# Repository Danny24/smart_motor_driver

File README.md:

# Smart Motor Driver
This motor driver is designed to be interfaced from a host microcontroller by I2C and be able to control the motor with a PID autonomously.

This is a smart motor driver designed to run a Pololu micro gearmotor, the objective of this board is to be able to implement a PID control over this motors with the corresponding RPM feedback using a hall effect sensor. So it must have his own microcontroller and H bridge to be capable of do the work by itself.

The host microcontroller (or any system that can use I2C) will communicate by I2C in order to give the commands to the smart driver module, this includes speed and direction of the motor. The module will automatically implement the PID to maintain the speed and apply more/less power in the motor to achieve that.

Also the control module will be capable of driving the motor for a desired distance and then stop when is reached. To do that you must specify the diameter of your wheel and the gearbox ratio.

This is a project under development, so please follow me to get updates :) This is an open source project, so if you have any ideas to improve it you are welcome!

Check out the project details on Hackaday: https://hackaday.io/project/158429-smart-motor-driver-for-robotics

Thank you for support :)

<br />This work is licensed under a <a rel="license" href="http://creativecommons.org/licenses/by-sa/2.0/">Creative Commons Attribution-ShareAlike 2.0 Generic License</a>.

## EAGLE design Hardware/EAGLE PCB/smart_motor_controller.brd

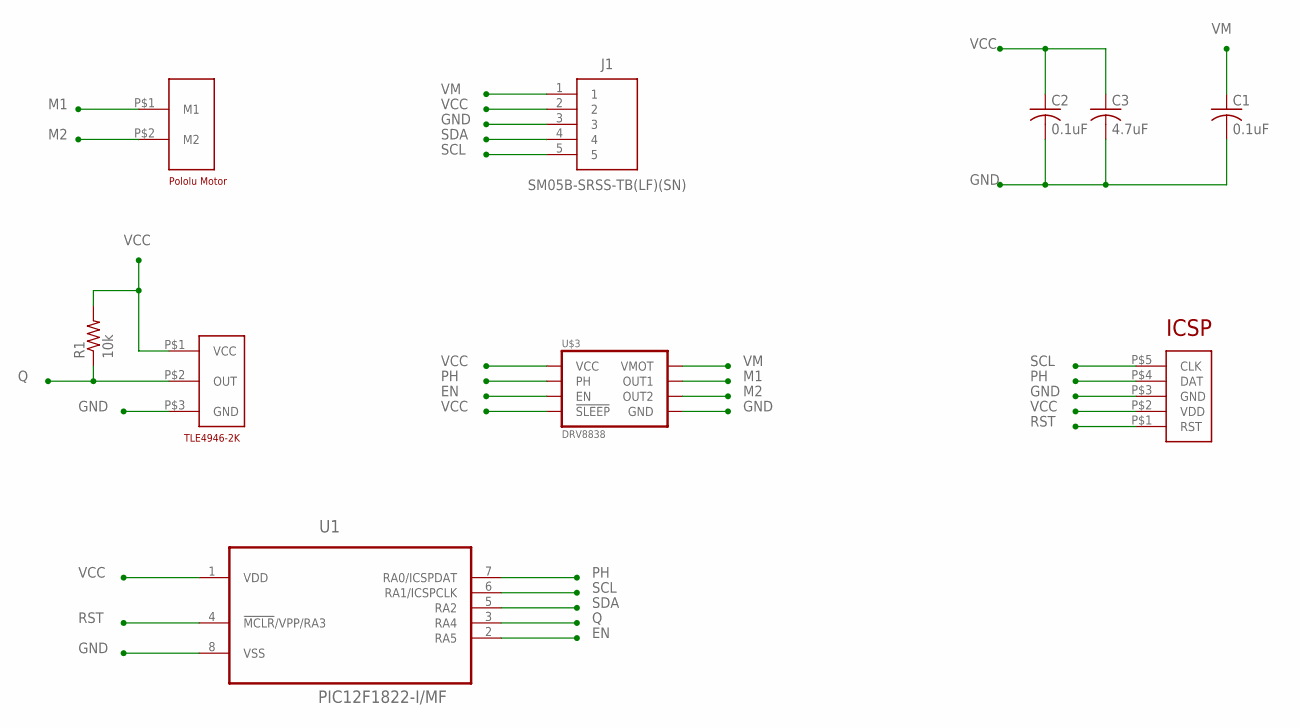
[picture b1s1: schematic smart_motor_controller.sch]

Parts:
C1, C2: 0.1uF; C0603K
C3: 4.7uF; C0805K
J1: SM05B-SRSS-TB(LF)(SN)
R1: 10k; R0805
U1: PIC12F1822-I/MF; DFN300X300X100-9N
U$1: ICSP_POGO
U$3: DRV8838; DSG
U$4: TLE4946-2K; SC59
U$5: POLOLU-MOTOR-BACK; POLOL-MOTOR-BACK

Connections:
EN: U1.2 (RA5), U$3.5 (EN)
GND: C1.2, C2.2, C3.2, J1.3, U1.8 (VSS), U$1.P$3 (GND), U$3.4 (GND), U$3.PAD (GND), U$4.P$3 (GND)
M1: U$3.2 (OUT1), U$5.P$1 (M1)
M2: U$3.3 (OUT2), U$5.P$2 (M2)
PH: U1.7 (RA0/ICSPDAT), U$1.P$4 (DAT), U$3.6 (PH)
Q: R1.1, U1.3 (RA4), U$4.P$2 (OUT)
RST: U1.4 (!MCLR!/VPP/RA3), U$1.P$1 (RST)
SCL: J1.5, U1.6 (RA1/ICSPCLK), U$1.P$5 (CLK)
SDA: J1.4, U1.5 (RA2)
VCC: C2.1, C3.1, J1.2, R1.2, U1.1 (VDD), U$1.P$2 (VDD), U$3.7 (!SLEEP), U$3.8 (VCC), U$4.P$1 (VCC)
VM: C1.1, J1.1, U$3.1 (VMOT)

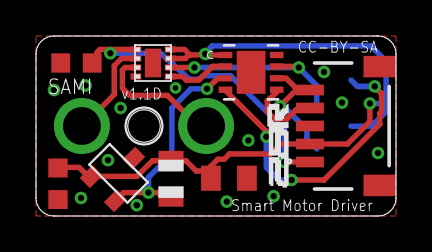
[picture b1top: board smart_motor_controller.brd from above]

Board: 2 copper layers, 20.0 x 10.0 mm, 10 parts (1 on the bottom side), 11 nets.

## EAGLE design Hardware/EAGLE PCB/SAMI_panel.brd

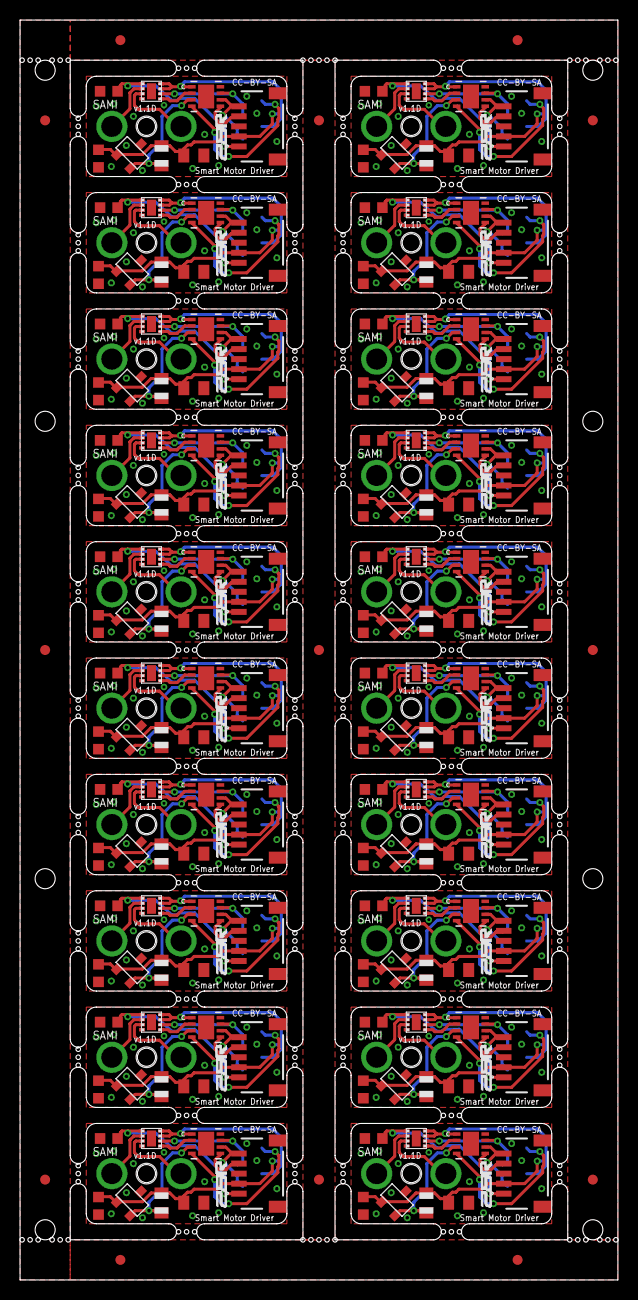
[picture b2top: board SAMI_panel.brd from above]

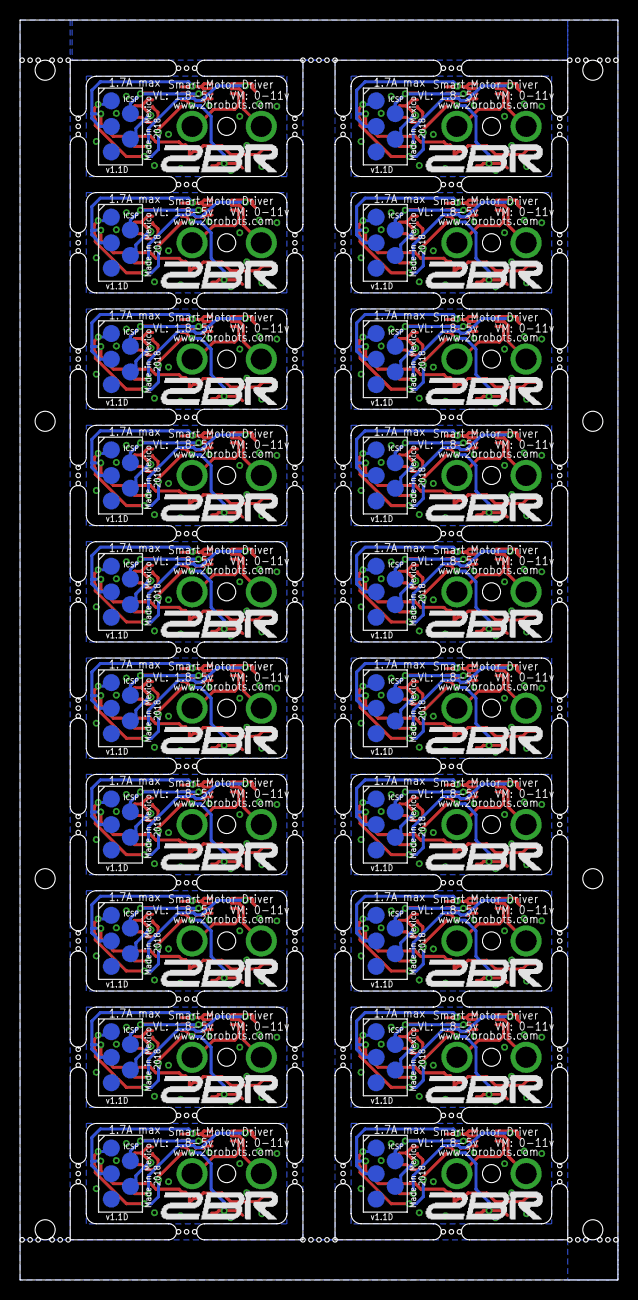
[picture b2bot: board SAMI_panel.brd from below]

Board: 2 copper layers, 59.6 x 125.6 mm, 213 parts (20 on the bottom side), 220 nets.

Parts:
C1, C2, C4, C5, C7, C8, C10, C11, C13, C14, C16, C17, C19, C20, C22, C23, C25, C26, C28, C29, C31, C32, C34, C35, C37, C38, C40, C41, C43, C44, C46, C47, C49, C50, C52, C53, C55, C56, C58, C59: 0.1uF; C0603K
C3, C6, C9, C12, C15, C18, C21, C24, C27, C30, C33, C36, C39, C42, C45, C48, C51, C54, C57, C60: 4.7uF; C0805K
E$1, E$2, E$3, E$4, E$5, E$6, E$7, E$8, E$9, E$10, E$11, E$12, E$13: FIDUCIAL
J1, J2, J3, J4, J5, J6, J7, J8, J9, J10, J11, J12, J13, J14, J15, J16, J17, J18, J19, J20: SM05B-SRSS-TB(LF)(SN)
R1, R2, R3, R4, R5, R6, R7, R8, R9, R10, R11, R12, R13, R14, R15, R16, R17, R18, R19, R20: 10k; R0805
U1, U2, U3, U4, U5, U6, U7, U8, U9, U10, U11, U12, U13, U14, U15, U16, U17, U18, U19, U20: PIC12F1822-I/MF; DFN300X300X100-9N
U$1, U$2, U$9, U$13, U$17, U$21, U$25, U$29, U$33, U$37, U$41, U$45, U$49, U$53, U$57, U$61, U$65, U$69, U$73, U$77: ICSP_POGO
U$3, U$6, U$10, U$14, U$18, U$22, U$26, U$30, U$34, U$38, U$42, U$46, U$50, U$54, U$58, U$62, U$66, U$70, U$74, U$78: DRV8838; DSG
U$4, U$7, U$11, U$15, U$19, U$23, U$27, U$31, U$35, U$39, U$43, U$47, U$51, U$55, U$59, U$63, U$67, U$71, U$75, U$79: TLE4946-2K; SC59
U$5, U$8, U$12, U$16, U$20, U$24, U$28, U$32, U$36, U$40, U$44, U$48, U$52, U$56, U$60, U$64, U$68, U$72, U$76, U$80: POLOLU-MOTOR-BACK; POLOL-MOTOR-BACK

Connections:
EN: U1.2, U$3.5
EN1: U2.2, U$6.5
EN2: U3.2, U$10.5
EN3: U4.2, U$14.5
EN4: U5.2, U$18.5
EN5: U6.2, U$22.5
EN6: U7.2, U$26.5
EN7: U8.2, U$30.5
EN8: U9.2, U$34.5
EN9: U10.2, U$38.5
EN10: U11.2, U$42.5
EN11: U12.2, U$46.5
EN12: U13.2, U$50.5
EN13: U14.2, U$54.5
EN14: U15.2, U$58.5
EN15: U16.2, U$62.5
EN16: U17.2, U$66.5
EN17: U18.2, U$70.5
EN18: U19.2, U$74.5
EN19: U20.2, U$78.5
GND: C1.2, C2.2, C3.2, J1.3, U1.8, U$1.P$3, U$3.4, U$3.PAD, U$4.P$3
GND1: C4.2, C5.2, C6.2, J2.3, U2.8, U$2.P$3, U$6.4, U$6.PAD, U$7.P$3
GND2: C7.2, C8.2, C9.2, J3.3, U3.8, U$9.P$3, U$10.4, U$10.PAD, U$11.P$3
GND3: C10.2, C11.2, C12.2, J4.3, U4.8, U$13.P$3, U$14.4, U$14.PAD, U$15.P$3
GND4: C13.2, C14.2, C15.2, J5.3, U5.8, U$17.P$3, U$18.4, U$18.PAD, U$19.P$3
GND5: C16.2, C17.2, C18.2, J6.3, U6.8, U$21.P$3, U$22.4, U$22.PAD, U$23.P$3
GND6: C19.2, C20.2, C21.2, J7.3, U7.8, U$25.P$3, U$26.4, U$26.PAD, U$27.P$3
GND7: C22.2, C23.2, C24.2, J8.3, U8.8, U$29.P$3, U$30.4, U$30.PAD, U$31.P$3
GND8: C25.2, C26.2, C27.2, J9.3, U9.8, U$33.P$3, U$34.4, U$34.PAD, U$35.P$3
GND9: C28.2, C29.2, C30.2, J10.3, U10.8, U$37.P$3, U$38.4, U$38.PAD, U$39.P$3
GND10: C31.2, C32.2, C33.2, J11.3, U11.8, U$41.P$3, U$42.4, U$42.PAD, U$43.P$3
GND11: C34.2, C35.2, C36.2, J12.3, U12.8, U$45.P$3, U$46.4, U$46.PAD, U$47.P$3
GND12: C37.2, C38.2, C39.2, J13.3, U13.8, U$49.P$3, U$50.4, U$50.PAD, U$51.P$3
GND13: C40.2, C41.2, C42.2, J14.3, U14.8, U$53.P$3, U$54.4, U$54.PAD, U$55.P$3
GND14: C43.2, C44.2, C45.2, J15.3, U15.8, U$57.P$3, U$58.4, U$58.PAD, U$59.P$3
GND15: C46.2, C47.2, C48.2, J16.3, U16.8, U$61.P$3, U$62.4, U$62.PAD, U$63.P$3
GND16: C49.2, C50.2, C51.2, J17.3, U17.8, U$65.P$3, U$66.4, U$66.PAD, U$67.P$3
GND17: C52.2, C53.2, C54.2, J18.3, U18.8, U$69.P$3, U$70.4, U$70.PAD, U$71.P$3
GND18: C55.2, C56.2, C57.2, J19.3, U19.8, U$73.P$3, U$74.4, U$74.PAD, U$75.P$3
GND19: C58.2, C59.2, C60.2, J20.3, U20.8, U$77.P$3, U$78.4, U$78.PAD, U$79.P$3
M1: U$3.2, U$5.P$1
M2: U$3.3, U$5.P$2
M3: U$6.3, U$8.P$2
M4: U$6.2, U$8.P$1
M5: U$10.3, U$12.P$2
M6: U$10.2, U$12.P$1
M7: U$14.3, U$16.P$2
M8: U$14.2, U$16.P$1
M9: U$18.3, U$20.P$2
M10: U$18.2, U$20.P$1
M11: U$22.3, U$24.P$2
M12: U$22.2, U$24.P$1
M13: U$26.3, U$28.P$2
M14: U$26.2, U$28.P$1
M15: U$30.3, U$32.P$2
M16: U$30.2, U$32.P$1
M17: U$34.3, U$36.P$2
M18: U$34.2, U$36.P$1
M19: U$38.3, U$40.P$2
M20: U$38.2, U$40.P$1
M21: U$42.3, U$44.P$2
M22: U$42.2, U$44.P$1
M23: U$46.3, U$48.P$2
M24: U$46.2, U$48.P$1
M25: U$50.3, U$52.P$2
M26: U$50.2, U$52.P$1
M27: U$54.3, U$56.P$2
M28: U$54.2, U$56.P$1
M29: U$58.3, U$60.P$2
M30: U$58.2, U$60.P$1
M31: U$62.3, U$64.P$2
M32: U$62.2, U$64.P$1
M33: U$66.3, U$68.P$2
M34: U$66.2, U$68.P$1
M35: U$70.3, U$72.P$2
M36: U$70.2, U$72.P$1
M37: U$74.3, U$76.P$2
M38: U$74.2, U$76.P$1
M39: U$78.3, U$80.P$2
M40: U$78.2, U$80.P$1
PH: U1.7, U$1.P$4, U$3.6
PH1: U2.7, U$2.P$4, U$6.6
PH2: U3.7, U$9.P$4, U$10.6
PH3: U4.7, U$13.P$4, U$14.6
PH4: U5.7, U$17.P$4, U$18.6
PH5: U6.7, U$21.P$4, U$22.6
PH6: U7.7, U$25.P$4, U$26.6
PH7: U8.7, U$29.P$4, U$30.6
PH8: U9.7, U$33.P$4, U$34.6
PH9: U10.7, U$37.P$4, U$38.6
PH10: U11.7, U$41.P$4, U$42.6
PH11: U12.7, U$45.P$4, U$46.6
PH12: U13.7, U$49.P$4, U$50.6
PH13: U14.7, U$53.P$4, U$54.6
PH14: U15.7, U$57.P$4, U$58.6
PH15: U16.7, U$61.P$4, U$62.6
PH16: U17.7, U$65.P$4, U$66.6
PH17: U18.7, U$69.P$4, U$70.6
PH18: U19.7, U$73.P$4, U$74.6
PH19: U20.7, U$77.P$4, U$78.6
Q: R1.1, U1.3, U$4.P$2
Q1: R2.1, U2.3, U$7.P$2
Q2: R3.1, U3.3, U$11.P$2
Q3: R4.1, U4.3, U$15.P$2
Q4: R5.1, U5.3, U$19.P$2
Q5: R6.1, U6.3, U$23.P$2
Q6: R7.1, U7.3, U$27.P$2
Q7: R8.1, U8.3, U$31.P$2
Q8: R9.1, U9.3, U$35.P$2
Q9: R10.1, U10.3, U$39.P$2
Q10: R11.1, U11.3, U$43.P$2
Q11: R12.1, U12.3, U$47.P$2
Q12: R13.1, U13.3, U$51.P$2
Q13: R14.1, U14.3, U$55.P$2
Q14: R15.1, U15.3, U$59.P$2
Q15: R16.1, U16.3, U$63.P$2
Q16: R17.1, U17.3, U$67.P$2
Q17: R18.1, U18.3, U$71.P$2
Q18: R19.1, U19.3, U$75.P$2
Q19: R20.1, U20.3, U$79.P$2
RST: U1.4, U$1.P$1
RST1: U2.4, U$2.P$1
RST2: U3.4, U$9.P$1
RST3: U4.4, U$13.P$1
RST4: U5.4, U$17.P$1
RST5: U6.4, U$21.P$1
RST6: U7.4, U$25.P$1
RST7: U8.4, U$29.P$1
RST8: U9.4, U$33.P$1
RST9: U10.4, U$37.P$1
RST10: U11.4, U$41.P$1
RST11: U12.4, U$45.P$1
RST12: U13.4, U$49.P$1
RST13: U14.4, U$53.P$1
RST14: U15.4, U$57.P$1
RST15: U16.4, U$61.P$1
RST16: U17.4, U$65.P$1
RST17: U18.4, U$69.P$1
RST18: U19.4, U$73.P$1
RST19: U20.4, U$77.P$1
SCL: J1.5, U1.6, U$1.P$5
SCL1: J2.5, U2.6, U$2.P$5
SCL2: J3.5, U3.6, U$9.P$5
SCL3: J4.5, U4.6, U$13.P$5
SCL4: J5.5, U5.6, U$17.P$5
SCL5: J6.5, U6.6, U$21.P$5
SCL6: J7.5, U7.6, U$25.P$5
SCL7: J8.5, U8.6, U$29.P$5
SCL8: J9.5, U9.6, U$33.P$5
SCL9: J10.5, U10.6, U$37.P$5
SCL10: J11.5, U11.6, U$41.P$5
SCL11: J12.5, U12.6, U$45.P$5
SCL12: J13.5, U13.6, U$49.P$5
SCL13: J14.5, U14.6, U$53.P$5
SCL14: J15.5, U15.6, U$57.P$5
SCL15: J16.5, U16.6, U$61.P$5
SCL16: J17.5, U17.6, U$65.P$5
SCL17: J18.5, U18.6, U$69.P$5
SCL18: J19.5, U19.6, U$73.P$5
SCL19: J20.5, U20.6, U$77.P$5
SDA: J1.4, U1.5
SDA1: J2.4, U2.5
SDA2: J3.4, U3.5
SDA3: J4.4, U4.5
SDA4: J5.4, U5.5
SDA5: J6.4, U6.5
SDA6: J7.4, U7.5
SDA7: J8.4, U8.5
SDA8: J9.4, U9.5
SDA9: J10.4, U10.5
SDA10: J11.4, U11.5
SDA11: J12.4, U12.5
SDA12: J13.4, U13.5
SDA13: J14.4, U14.5
SDA14: J15.4, U15.5
SDA15: J16.4, U16.5
SDA16: J17.4, U17.5
SDA17: J18.4, U18.5
SDA18: J19.4, U19.5
SDA19: J20.4, U20.5
VCC: C2.1, C3.1, J1.2, R1.2, U1.1, U$1.P$2, U$3.7, U$3.8, U$4.P$1
VCC1: C5.1, C6.1, J2.2, R2.2, U2.1, U$2.P$2, U$6.7, U$6.8, U$7.P$1
VCC2: C8.1, C9.1, J3.2, R3.2, U3.1, U$9.P$2, U$10.7, U$10.8, U$11.P$1
VCC3: C11.1, C12.1, J4.2, R4.2, U4.1, U$13.P$2, U$14.7, U$14.8, U$15.P$1
VCC4: C14.1, C15.1, J5.2, R5.2, U5.1, U$17.P$2, U$18.7, U$18.8, U$19.P$1
VCC5: C17.1, C18.1, J6.2, R6.2, U6.1, U$21.P$2, U$22.7, U$22.8, U$23.P$1
VCC6: C20.1, C21.1, J7.2, R7.2, U7.1, U$25.P$2, U$26.7, U$26.8, U$27.P$1
VCC7: C23.1, C24.1, J8.2, R8.2, U8.1, U$29.P$2, U$30.7, U$30.8, U$31.P$1
VCC8: C26.1, C27.1, J9.2, R9.2, U9.1, U$33.P$2, U$34.7, U$34.8, U$35.P$1
VCC9: C29.1, C30.1, J10.2, R10.2, U10.1, U$37.P$2, U$38.7, U$38.8, U$39.P$1
VCC10: C32.1, C33.1, J11.2, R11.2, U11.1, U$41.P$2, U$42.7, U$42.8, U$43.P$1
VCC11: C35.1, C36.1, J12.2, R12.2, U12.1, U$45.P$2, U$46.7, U$46.8, U$47.P$1
VCC12: C38.1, C39.1, J13.2, R13.2, U13.1, U$49.P$2, U$50.7, U$50.8, U$51.P$1
VCC13: C41.1, C42.1, J14.2, R14.2, U14.1, U$53.P$2, U$54.7, U$54.8, U$55.P$1
VCC14: C44.1, C45.1, J15.2, R15.2, U15.1, U$57.P$2, U$58.7, U$58.8, U$59.P$1
VCC15: C47.1, C48.1, J16.2, R16.2, U16.1, U$61.P$2, U$62.7, U$62.8, U$63.P$1
VCC16: C50.1, C51.1, J17.2, R17.2, U17.1, U$65.P$2, U$66.7, U$66.8, U$67.P$1
VCC17: C53.1, C54.1, J18.2, R18.2, U18.1, U$69.P$2, U$70.7, U$70.8, U$71.P$1
VCC18: C56.1, C57.1, J19.2, R19.2, U19.1, U$73.P$2, U$74.7, U$74.8, U$75.P$1
VCC19: C59.1, C60.1, J20.2, R20.2, U20.1, U$77.P$2, U$78.7, U$78.8, U$79.P$1
VM: C1.1, J1.1, U$3.1
VM1: C4.1, J2.1, U$6.1
VM2: C7.1, J3.1, U$10.1
VM3: C10.1, J4.1, U$14.1
VM4: C13.1, J5.1, U$18.1
VM5: C16.1, J6.1, U$22.1
VM6: C19.1, J7.1, U$26.1
VM7: C22.1, J8.1, U$30.1
VM8: C25.1, J9.1, U$34.1
VM9: C28.1, J10.1, U$38.1
VM10: C31.1, J11.1, U$42.1
VM11: C34.1, J12.1, U$46.1
VM12: C37.1, J13.1, U$50.1
VM13: C40.1, J14.1, U$54.1
VM14: C43.1, J15.1, U$58.1
VM15: C46.1, J16.1, U$62.1
VM16: C49.1, J17.1, U$66.1
VM17: C52.1, J18.1, U$70.1
VM18: C55.1, J19.1, U$74.1
VM19: C58.1, J20.1, U$78.1

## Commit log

2018-03-19 Initialization
    First files published for this repo, in this edition the pcb is complete and the software is under development.
2018-03-19 add datasheet and photo
2018-06-19 Main program update
2018-06-24 Alfa code update
2018-06-26 PID fully working
2018-06-26 Typo correct
2018-07-09 added mplab code
2018-07-10 corrections mplab
2018-07-11 bugfix
    An error that suddenly stops the motor when change direction command was triggered is fixed and now brakes the motor using PID before changing direction to prevent damaged gears
2018-07-11 Update LICENSE
2018-07-18 License changed to CC-BY-NC-SA 4.0
2018-07-22 auto stop experiment
2018-07-25 i2C_testing
2018-08-10 PCB files updated and added 3D model
2018-09-04 mixed i2c and pid
2018-09-05 Update PID calculation
2018-09-06 improved PID and size reduction
2018-09-15 add mode support and eeprom save
2018-09-16 beta release, fully working. Maybe some bugs
2018-09-17 bugfixes
2018-09-30 touch up
2018-11-01 updates
    correction of some files and also added the pcb for a panel production
2020-08-19 Update README.md
    Suggesting some grammar improvements.

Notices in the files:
Hardware/EAGLE PCB/SAMI_panel.brd:
CC-BY-SA
